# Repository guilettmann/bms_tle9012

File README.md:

# BMS TLE9012

Battery management system for the **AMPERA** Formula SAE electric car (AMP 227).

## What it is

- **Slave board** (`bms-amp-227/`): KiCad, 6 layers, 110 × 85 mm, 28S. Four
  **TLE9012DQU** cell-supervisor ICs (7 cells each) measure cell voltages and
  temperatures (16 NTCs) and drive external passive balancing (PMOS + resistors).
  The four ICs are daisy-chained over capacitively isolated **iso UART**, with a
  transformer at the cable input. Each IC has its own floating ground. The board
  has a 4 mm isolation barrier.
- **Firmware** (`firmware/`): STM32G491 (developed on a NUCLEO-G491RE). It talks to
  the chain through a **TLE9015DQU** iso UART transceiver. The goal is a
  parameterizable firmware with a CAN bootloader.
- **Simulations** (`sim/`): LTspice models (balancing).
- **Docs** (`docs/`): project reports.

## License

MIT. See [LICENSE](LICENSE).

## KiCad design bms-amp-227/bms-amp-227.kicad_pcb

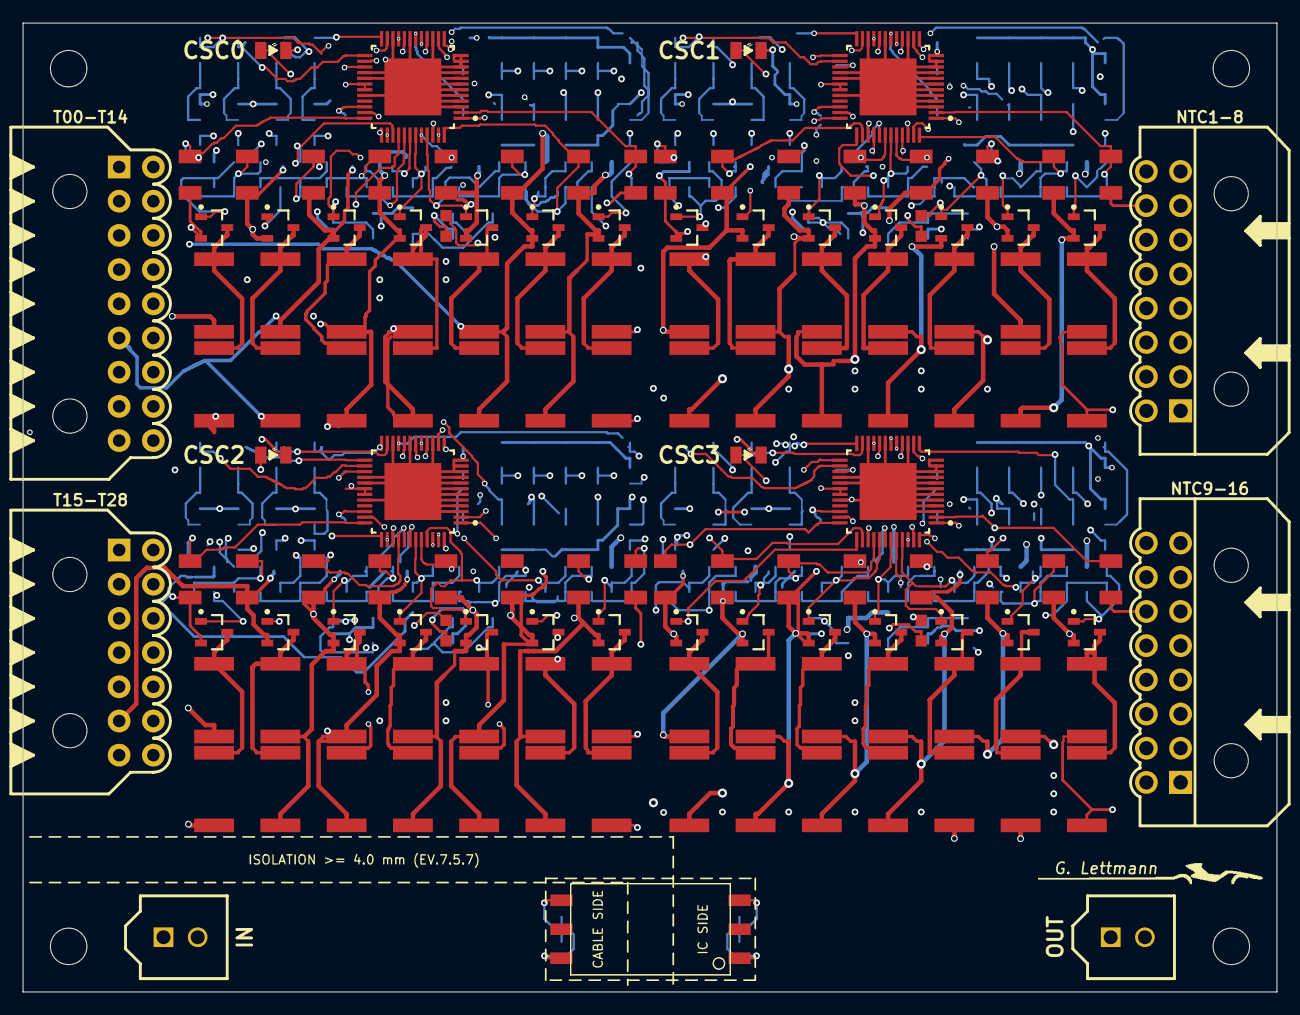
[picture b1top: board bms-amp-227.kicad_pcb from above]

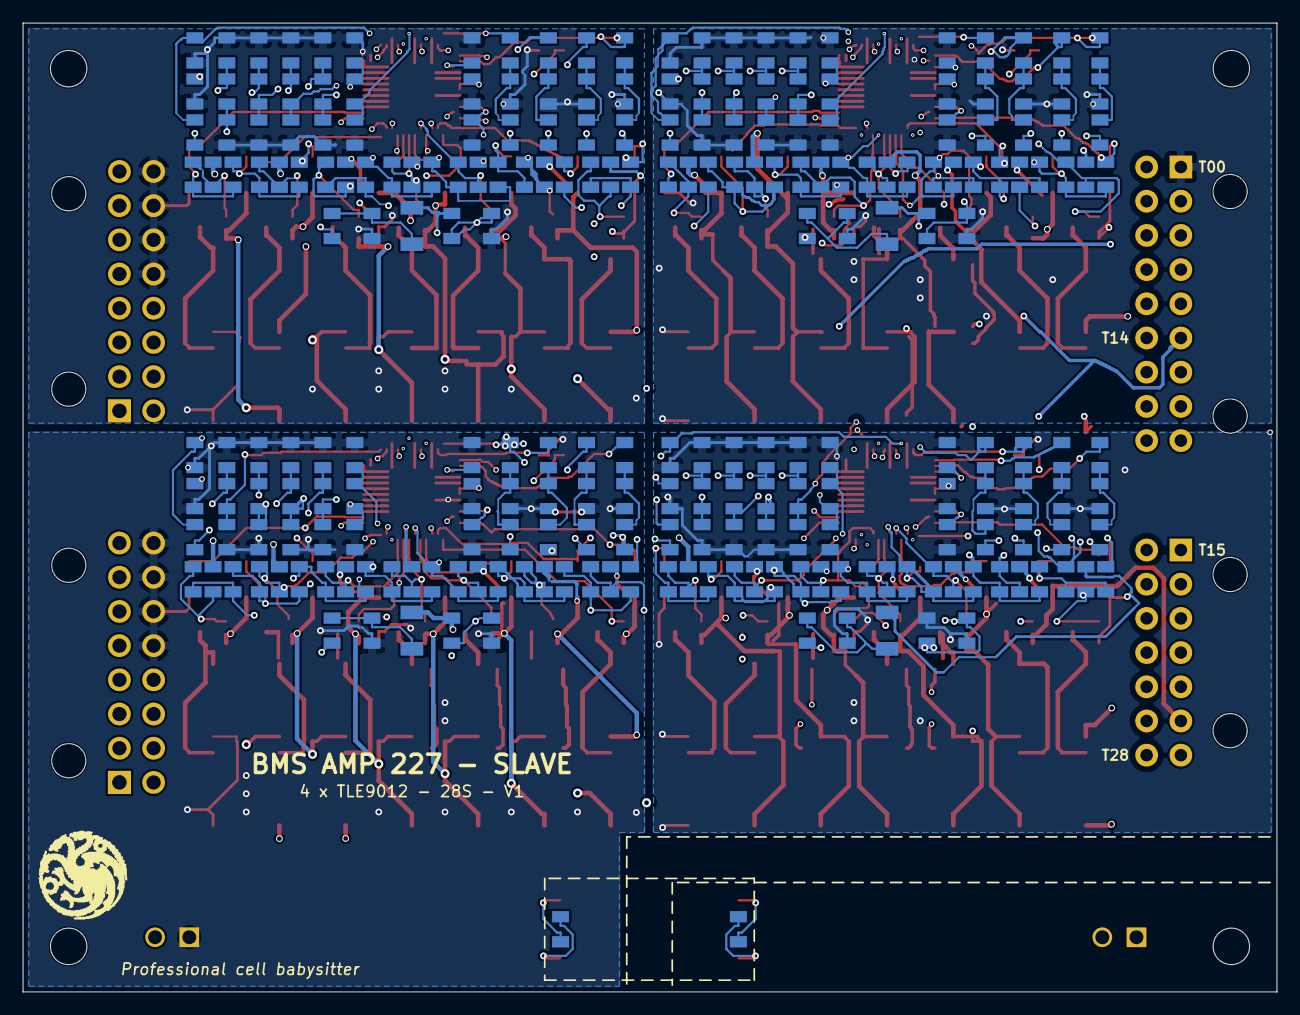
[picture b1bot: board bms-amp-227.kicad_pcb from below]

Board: 6 copper layers, 110.0 x 85.0 mm, 379 parts (239 on the bottom side), 233 nets.

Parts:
ART1: ART_DRAGON
ART2: ART_CAR
C1, C2, C9, C10, C11, C14, C15, C18, C38, C39, C46, C47, C48, C51, C52, C55, C75, C76, C83, C84, C85, C88, C89, C92, C112, C113, C120, C121, C122, C125, C126, C129: 330nF; SMD0805C
C3, C4, C12, C13, C16, C17, C19, C40, C41, C49, C50, C53, C54, C56, C77, C78, C86, C87, C90, C91, C93, C114, C115, C123, C124, C127, C128, C130: 1nF; SMD0805C
C5, C6, C42, C43, C79, C80, C116, C117: 100nF/100V; SMD0805C
C7, C20, C21, C24, C25, C44, C57, C58, C61, C62, C81, C94, C95, C98, C99, C118, C131, C132, C135, C136: 1nF/100V; SMD0805C
C8, C45, C82, C119: 100nF; SMD0805C
C22, C23, C26, C27, C59, C60, C63, C64, C96, C97, C100, C101, C133, C134, C137, C138: 220pF/50V; SMD0805C
C28, C30, C32, C34, C36, C65, C67, C69, C71, C73, C102, C104, C106, C108, C110, C139, C141, C143, C145, C147: 4.7nF; SMD0805C
C29, C31, C33, C35, C37, C66, C68, C70, C72, C74, C103, C105, C107, C109, C111, C140, C142, C144, C146, C148: 10nF; SMD0805C
D1, D2, D3, D4: LED; SMD0805LED
H1, H2, H3, H4: MountingHole_3.2mm_M3
J1: HM2108NL
J2: MicroFit DR 9x2; MICRO-FIT 9X2 MULT 90º
J3, J4: MicroFit DR 8x2; Micro-Fit Dual Row 16 POS 90°
J5: MicroFit DR 7x2; MICRO-FIT 7X2 MULT 90º
J6, J7: MicroFit DR 1x2; MICRO-FIT 2X1 180° TE
Q1, Q2, Q3, Q4, Q5, Q6, Q7, Q8, Q9, Q10, Q11, Q12, Q13, Q14, Q15, Q16, Q17, Q18, Q19, Q20, Q21, Q22, Q23, Q24, Q25, Q26, Q27, Q28: BSS215P H6327; INF-PG-SOT23_N
R1, R2, R11, R14, R15, R16, R23, R24, R31, R47, R48, R57, R60, R61, R62, R69, R70, R77, R91, R92, R101, R104, R105, R106, R113, R114, R121, R135, R136, R145, R148, R149, R150, R157, R158, R165: 10R; SMD1206R
R3, R4, R49, R93, R137, R138, R180, R182: 33k; SMD0805R
R5, R6, R17, R18, R25, R26, R32, R51, R52, R63, R64, R71, R72, R78, R95, R96, R107, R108, R115, R116, R122, R139, R140, R151, R152, R159, R160, R166: 10k; SMD0805R
R7, R8, R9, R10, R19, R20, R21, R22, R27, R28, R29, R30, R33, R34, R53, R54, R55, R56, R65, R66, R67, R68, R73, R74, R75, R76, R79, R80, R97, R98, R99, R100, R109, R110, R111, R112, R117, R118, R119, R120, R123, R124, R141, R142, R143, R144, R153, R154, R155, R156, R161, R162, R163, R164, R167, R168: 18R; SMD2512R
R12, R13, R58, R59, R102, R103, R146, R147: 5R1; SMD0805R
R35, R36, R37, R38, R81, R82, R83, R84, R125, R126, R127, R128, R169, R170, R171, R172: 39R; SMD0805R
R39, R40, R41, R42, R45, R85, R86, R87, R88, R89, R129, R130, R131, R132, R133, R173, R174, R175, R176, R177: 100R; SMD0805R
R43, R44: 1k; SMD0805R
R46, R90, R134, R178: NTC; SMD0603R
R50, R94, R179, R181: 680R; SMD0805R
U1, U2, U3, U4: TLE9012DQUXUMA1; FP-PG-TQFP-48-MFG

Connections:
G05_0: C3.2, Q1.1, R5.1, U1.1
G05_1: C40.2, Q8.1, R51.1, U2.1
G05_2: C77.2, Q15.1, R95.1, U3.1
G05_3: C114.2, Q22.1, R139.1, U4.1
G06_0: C4.2, Q2.1, R6.1, U1.47
G06_1: C41.2, Q9.1, R52.1, U2.47
G06_2: C78.2, Q16.1, R96.1, U3.47
G06_3: C115.2, Q23.1, R140.1, U4.47
G07_0: C12.2, Q3.1, R17.1, U1.45
G07_1: C49.2, Q10.1, R63.1, U2.45
G07_2: C86.2, Q17.1, R107.1, U3.45
G07_3: C123.2, Q24.1, R151.1, U4.45
G08_0: C13.2, Q4.1, R18.1, U1.43
G08_1: C50.2, Q11.1, R64.1, U2.43
G08_2: C87.2, Q18.1, R108.1, U3.43
G08_3: C124.2, Q25.1, R152.1, U4.43
G09_0: C16.2, Q5.1, R25.1, U1.41
G09_1: C53.2, Q12.1, R71.1, U2.41
G09_2: C90.2, Q19.1, R115.1, U3.41
G09_3: C127.2, Q26.1, R159.1, U4.41
G10_0: C17.2, Q6.1, R26.1, U1.39
G10_1: C54.2, Q13.1, R72.1, U2.39
G10_2: C91.2, Q20.1, R116.1, U3.39
G10_3: C128.2, Q27.1, R160.1, U4.39
G11_0: C19.2, Q7.1, R32.1, U1.37
G11_1: C56.2, Q14.1, R78.1, U2.37
G11_2: C93.2, Q21.1, R122.1, U3.37
G11_3: C130.2, Q28.1, R166.1, U4.37
IFH_H_0: R36.2, U1.25
IFH_H_1: R82.2, U2.25
IFH_H_2: R126.2, U3.25
IFH_H_3: R170.2, U4.25
IFH_L_0: R38.2, U1.26
IFH_L_1: R84.2, U2.26
IFH_L_2: R128.2, U3.26
IFH_L_3: R172.2, U4.26
IFL_H_0: R35.2, U1.24
IFL_H_1: R81.2, U2.24
IFL_H_2: R125.2, U3.24
IFL_H_3: R169.2, U4.24
IFL_L_0: R37.2, U1.23
IFL_L_1: R83.2, U2.23
IFL_L_2: R127.2, U3.23
IFL_L_3: R171.2, U4.23
ISO01_H: C21.1, C57.1
ISO01_L: C25.1, C61.1
ISO12_H: C58.1, C94.1
ISO12_L: C62.1, C98.1
ISO23_H: C95.1, C131.1
ISO23_L: C99.1, C135.1
ISO_IN_H: C20.1, J1.1, R43.2
ISO_IN_L: C24.1, J1.3, R43.1
NTC1: C28.2, J3.1, R39.1
NTC2: C30.2, J3.2, R40.1
NTC3: C32.2, J3.3, R41.1
NTC4: C34.2, J3.4, R42.1
NTC5: C65.2, J3.5, R85.1
NTC6: C67.2, J3.6, R86.1
NTC7: C69.2, J3.7, R87.1
NTC8: C71.2, J3.8, R88.1
NTC9: C102.2, J4.1, R129.1
NTC10: C104.2, J4.2, R130.1
NTC11: C106.2, J4.3, R131.1
NTC12: C108.2, J4.4, R132.1
NTC13: C139.2, J4.5, R173.1
NTC14: C141.2, J4.6, R174.1
NTC15: C143.2, J4.7, R175.1
NTC16: C145.2, J4.8, R176.1
NetC5_2: C5.2, R11.1, R12.2
NetC8_2: C8.2, U1.30, U1.31
NetC11_1: C11.1, U1.27
NetC20_2: C20.2, C22.2, R35.1
NetC21_2: C21.2, C23.2, R36.1
NetC24_2: C24.2, C26.2, R37.1
NetC25_2: C25.2, C27.2, R38.1
NetC36_2: C36.2, R45.1, R46.2
NetC42_2: C42.2, R57.1, R58.2
NetC45_2: C45.2, U2.30, U2.31
NetC48_1: C48.1, U2.27
NetC57_2: C57.2, C59.2, R81.1
NetC58_2: C58.2, C60.2, R82.1
NetC61_2: C61.2, C63.2, R83.1
NetC62_2: C62.2, C64.2, R84.1
NetC73_2: C73.2, R89.1, R90.2
NetC79_2: C79.2, R101.1, R102.2
NetC82_2: C82.2, U3.30, U3.31
NetC85_1: C85.1, U3.27
NetC94_2: C94.2, C96.2, R125.1
NetC95_2: C95.2, C97.2, R126.1
NetC98_2: C98.2, C100.2, R127.1
NetC99_2: C99.2, C101.2, R128.1
NetC110_2: C110.2, R133.1, R134.2
NetC116_2: C116.2, R145.1, R146.2
NetC119_2: C119.2, U4.30, U4.31
NetC122_1: C122.1, U4.27
NetC131_2: C131.2, C133.2, R169.1
NetC132_2: C132.2, C134.2, R170.1
NetC135_2: C135.2, C137.2, R171.1
NetC136_2: C136.2, C138.2, R172.1
NetC147_2: C147.2, R177.1, R178.2
NetD1_1: D1.1, R50.1
NetD2_1: D2.1, R94.1
NetD3_1: D3.1, R179.1
NetD4_1: D4.1, R181.1
NetQ1_3: Q1.3, R7.2, R8.2
NetQ2_3: Q2.3, R9.2, R10.2
NetQ3_3: Q3.3, R19.2, R20.2
NetQ4_3: Q4.3, R21.2, R22.2
NetQ5_3: Q5.3, R27.2, R28.2
NetQ6_3: Q6.3, R29.2, R30.2
NetQ7_3: Q7.3, R33.2, R34.2
NetQ8_3: Q8.3, R53.2, R54.2
NetQ9_3: Q9.3, R55.2, R56.2
NetQ10_3: Q10.3, R65.2, R66.2
NetQ11_3: Q11.3, R67.2, R68.2
NetQ12_3: Q12.3, R73.2, R74.2
NetQ13_3: Q13.3, R75.2, R76.2
NetQ14_3: Q14.3, R79.2, R80.2
NetQ15_3: Q15.3, R97.2, R98.2
NetQ16_3: Q16.3, R99.2, R100.2
NetQ17_3: Q17.3, R109.2, R110.2
NetQ18_3: Q18.3, R111.2, R112.2
NetQ19_3: Q19.3, R117.2, R118.2
NetQ20_3: Q20.3, R119.2, R120.2
NetQ21_3: Q21.3, R123.2, R124.2
NetQ22_3: Q22.3, R141.2, R142.2
NetQ23_3: Q23.3, R143.2, R144.2
NetQ24_3: Q24.3, R153.2, R154.2
NetQ25_3: Q25.3, R155.2, R156.2
NetQ26_3: Q26.3, R161.2, R162.2
NetQ27_3: Q27.3, R163.2, R164.2
NetQ28_3: Q28.3, R167.2, R168.2
PWM0_0: R4.2, R50.2, U1.21
PWM0_1: R94.2, R138.2, U2.21
PWM0_2: R179.2, R180.2, U3.21
PWM0_3: R181.2, R182.2, U4.21
PWM1_0: R3.2, U1.20
PWM1_1: R49.2, U2.20
PWM1_2: R93.2, U3.20
PWM1_3: R137.2, U4.20
T00: C5.1, C6.1, C7.1, C8.1, C11.2, C22.1, C23.1, C26.1, C27.1, C28.1, C29.1, C30.1, C31.1, C32.1, C33.1, C34.1, C35.1, C36.1, C37.1, D1.2, J2.1, J3.13, J3.14, J3.15, J3.16, R3.1, R4.1, R7.1, R8.1, R14.2, R46.1, U1.3, U1.4, U1.5, U1.6, U1.7, U1.8, U1.9, U1.10, U1.11, U1.12, U1.15, U1.19, U1.22, U1.28, U1.29, U1.32, U1.49
T01: J2.2, Q1.2, R1.2, R5.2, R9.1, R10.1
T02: J2.3, Q2.2, R2.2, R6.2, R19.1, R20.1
T03: J2.4, Q3.2, R15.2, R17.2, R21.1, R22.1
T04: J2.5, Q4.2, R16.2, R18.2, R27.1, R28.1
T05: J2.6, Q5.2, R23.2, R25.2, R29.1, R30.1
T06: J2.7, Q6.2, R24.2, R26.2, R33.1, R34.1
T07: C42.1, C43.1, C44.1, C45.1, C48.2, C59.1, C60.1, C63.1, C64.1, C65.1, C66.1, C67.1, C68.1, C69.1, C70.1, C71.1, C72.1, C73.1, C74.1, D2.2, J2.8, J3.9, J3.10, J3.11, J3.12, Q7.2, R11.2, R13.2, R31.2, R32.2, R49.1, R53.1, R54.1, R60.2, R90.1, R138.1, U2.3, U2.4, U2.5, U2.6, U2.7, U2.8, U2.9, U2.10, U2.11, U2.12, U2.15, U2.19, U2.22, U2.28, U2.29, U2.32, U2.49
T08: J2.9, Q8.2, R47.2, R51.2, R55.1, R56.1
T09: J2.18, Q9.2, R48.2, R52.2, R65.1, R66.1
T10: J2.17, Q10.2, R61.2, R63.2, R67.1, R68.1
T11: J2.16, Q11.2, R62.2, R64.2, R73.1, R74.1
T12: J2.15, Q12.2, R69.2, R71.2, R75.1, R76.1
T13: J2.14, Q13.2, R70.2, R72.2, R79.1, R80.1
T14: C79.1, C80.1, C81.1, C82.1, C85.2, C96.1, C97.1, C100.1, C101.1, C102.1, C103.1, C104.1, C105.1, C106.1, C107.1, C108.1, C109.1, C110.1, C111.1, D3.2, J2.13, J4.13, J4.14, J4.15, J4.16, Q14.2, R57.2, R59.2, R77.2, R78.2, R93.1, R97.1, R98.1, R103.2, R104.2, R134.1, R180.1, U3.3, U3.4, U3.5, U3.6, U3.7, U3.8, U3.9, U3.10, U3.11, U3.12, U3.15, U3.19, U3.22, U3.28, U3.29, U3.32, U3.49
T15: J5.1, Q15.2, R91.2, R95.2, R99.1, R100.1
T16: J5.2, Q16.2, R92.2, R96.2, R109.1, R110.1
T17: J5.3, Q17.2, R105.2, R107.2, R111.1, R112.1
T18: J5.4, Q18.2, R106.2, R108.2, R117.1, R118.1
T19: J5.5, Q19.2, R113.2, R115.2, R119.1, R120.1
T20: J5.6, Q20.2, R114.2, R116.2, R123.1, R124.1
T21: C116.1, C117.1, C118.1, C119.1, C122.2, C133.1, C134.1, C137.1, C138.1, C139.1, C140.1, C141.1, C142.1, C143.1, C144.1, C145.1, C146.1, C147.1, C148.1, D4.2, J4.9, J4.10, J4.11, J4.12, J5.7, Q21.2, R101.2, R121.2, R122.2, R137.1, R141.1, R142.1, R148.2, R178.1, R182.1, U4.3, U4.4, U4.5, U4.6, U4.7, U4.8, U4.9, U4.10, U4.11, U4.12, U4.15, U4.19, U4.22, U4.28, U4.29, U4.32, U4.49
T22: J5.14, Q22.2, R135.2, R139.2, R143.1, R144.1
T23: J5.13, Q23.2, R136.2, R140.2, R153.1, R154.1
T24: J5.12, Q24.2, R149.2, R151.2, R155.1, R156.1
T25: J5.11, Q25.2, R150.2, R152.2, R161.1, R162.1
T26: J5.10, Q26.2, R157.2, R159.2, R163.1, R164.1
T27: J5.9, Q27.2, R158.2, R160.2, R167.1, R168.1
T28: J5.8, Q28.2, R145.2, R147.2, R165.2, R166.2
TMP0_0: C37.2, R45.2, U1.18
TMP0_1: C74.2, R89.2, U2.18
TMP0_2: C111.2, R133.2, U3.18
TMP0_3: C148.2, R177.2, U4.18
TMP1_0: C29.2, R39.2, U1.17
TMP1_1: C66.2, R85.2, U2.17
TMP1_2: C103.2, R129.2, U3.17
TMP1_3: C140.2, R173.2, U4.17
TMP2_0: C31.2, R40.2, U1.16
TMP2_1: C68.2, R86.2, U2.16
TMP2_2: C105.2, R130.2, U3.16
TMP2_3: C142.2, R174.2, U4.16
TMP3_0: C33.2, R41.2, U1.14
TMP3_1: C70.2, R87.2, U2.14
TMP3_2: C107.2, R131.2, U3.14
TMP3_3: C144.2, R175.2, U4.14
TMP4_0: C35.2, R42.2, U1.13
TMP4_1: C72.2, R88.2, U2.13
TMP4_2: C109.2, R132.2, U3.13
TMP4_3: C146.2, R176.2, U4.13
U05_0: C1.1, C3.1, R14.1, U1.2
U05_1: C38.1, C40.1, R60.1, U2.2
U05_2: C75.1, C77.1, R104.1, U3.2
U05_3: C112.1, C114.1, R148.1, U4.2
U06_0: C1.2, C2.1, C4.1, R1.1, U1.48
U06_1: C38.2, C39.1, C41.1, R47.1, U2.48
U06_2: C75.2, C76.1, C78.1, R91.1, U3.48
U06_3: C112.2, C113.1, C115.1, R135.1, U4.48
U07_0: C2.2, C9.1, C12.1, R2.1, U1.46
U07_1: C39.2, C46.1, C49.1, R48.1, U2.46
U07_2: C76.2, C83.1, C86.1, R92.1, U3.46
U07_3: C113.2, C120.1, C123.1, R136.1, U4.46
U08_0: C9.2, C10.1, C13.1, R15.1, U1.44
U08_1: C46.2, C47.1, C50.1, R61.1, U2.44
U08_2: C83.2, C84.1, C87.1, R105.1, U3.44
U08_3: C120.2, C121.1, C124.1, R149.1, U4.44
U09_0: C10.2, C14.1, C16.1, R16.1, U1.42
U09_1: C47.2, C51.1, C53.1, R62.1, U2.42
U09_2: C84.2, C88.1, C90.1, R106.1, U3.42
U09_3: C121.2, C125.1, C127.1, R150.1, U4.42
U10_0: C14.2, C15.1, C17.1, R23.1, U1.40
U10_1: C51.2, C52.1, C54.1, R69.1, U2.40
U10_2: C88.2, C89.1, C91.1, R113.1, U3.40
U10_3: C125.2, C126.1, C128.1, R157.1, U4.40
U11_0: C15.2, C18.1, C19.1, R24.1, U1.38
U11_1: C52.2, C55.1, C56.1, R70.1, U2.38
U11_2: C89.2, C92.1, C93.1, R114.1, U3.38
U11_3: C126.2, C129.1, C130.1, R158.1, U4.38
U12P_0: R12.1, U1.35
U12P_1: R58.1, U2.35
U12P_2: R102.1, U3.35
U12P_3: R146.1, U4.35
U12_0: C18.2, R31.1, U1.36
U12_1: C55.2, R77.1, U2.36
U12_2: C92.2, R121.1, U3.36
U12_3: C129.2, R165.1, U4.36
VS_0: C6.2, C7.2, R13.1, U1.34
VS_1: C43.2, C44.2, R59.1, U2.34
VS_2: C80.2, C81.2, R103.1, U3.34
VS_3: C117.2, C118.2, R147.1, U4.34
WIRE_IN_H: J1.6, J6.1, R44.2
WIRE_IN_L: J1.4, J6.2, R44.1
WIRE_OUT_H: C132.1, J7.1
WIRE_OUT_L: C136.1, J7.2
